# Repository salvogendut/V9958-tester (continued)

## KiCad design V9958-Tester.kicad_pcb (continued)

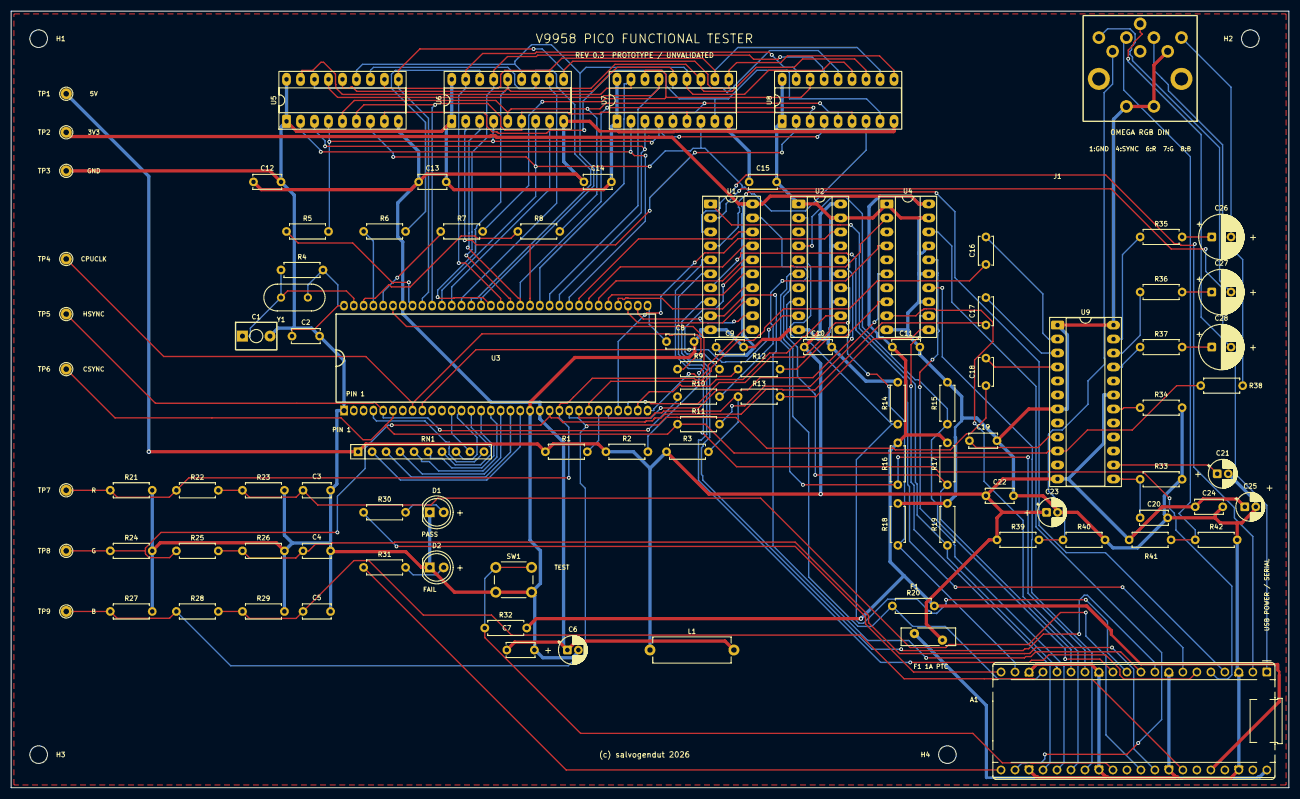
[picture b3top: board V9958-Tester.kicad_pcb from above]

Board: 2 copper layers, 232.0 x 141.0 mm, 101 parts (0 on the bottom side), 116 nets.

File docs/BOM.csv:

Quantity,References,Value / part,KiCad footprint,Notes
1,A1,Raspberry Pi Pico,Module:RaspberryPi_Pico_Common_THT,Original RP2040 Pico module; fit using two 1x20 THT socket strips
1,C1,30pF trimmer,V9958-Tester:C_Trim_P5.00mm,"2-pin ceramic trimmer, 5.0 mm pitch"
1,C2,22pF,Capacitor_THT:C_Disc_D5.0mm_W2.5mm_P5.00mm,
3,C3 C4 C5,10n,Capacitor_THT:C_Disc_D5.0mm_W2.5mm_P5.00mm,
1,C6,100uF,Capacitor_THT:CP_Radial_D5.0mm_P2.00mm,
13,C7 C9 C10 C11 C12 C13 C14 C15 C16 C17 C18 C19 C20,100n,Capacitor_THT:C_Disc_D5.0mm_W2.5mm_P5.00mm,
1,C8,100n VBB,Capacitor_THT:C_Disc_D5.0mm_W2.5mm_P5.00mm,
1,C21,10uF,Capacitor_THT:CP_Radial_D5.0mm_P2.00mm,
1,C22,100n VCC1,Capacitor_THT:C_Disc_D5.0mm_W2.5mm_P5.00mm,
1,C23,47uF VCC1,Capacitor_THT:CP_Radial_D5.0mm_P2.00mm,
1,C24,100n VCC2,Capacitor_THT:C_Disc_D5.0mm_W2.5mm_P5.00mm,
1,C25,47uF VCC2,Capacitor_THT:CP_Radial_D5.0mm_P2.00mm,
3,C26 C27 C28,220uF,Capacitor_THT:CP_Radial_D8.0mm_P3.50mm,
1,D1,GREEN PASS,LED_THT:LED_D5.0mm,
1,D2,RED FAIL,LED_THT:LED_D5.0mm,
1,F1,Bourns MF-RHT100 PTC 1.0A,Fuse:Fuse_Bourns_MF-RHT100,1.0 A hold / 1.8 A trip resettable fuse
4,H1 H2 H3 H4,M3,MountingHole:MountingHole_3.2mm_M3,
1,J1,OMEGA RGB DIN-8,V9958-Tester:DIN8_Omega_THT,Omega-compatible THT DIN-8 socket; verify the chosen part against the supplied footprint
1,L1,5.6uH,Inductor_THT:L_Axial_L14.0mm_D4.5mm_P15.24mm_Horizontal_Fastron_LACC,
12,R1 R2 R3 R14 R15 R16 R17 R18 R19 R20 R32 R40,10k,Resistor_THT:R_Axial_DIN0207_L6.3mm_D2.5mm_P7.62mm_Horizontal,
1,R4,470k,Resistor_THT:R_Axial_DIN0207_L6.3mm_D2.5mm_P7.62mm_Horizontal,
4,R5 R6 R7 R8,100,Resistor_THT:R_Axial_DIN0207_L6.3mm_D2.5mm_P7.62mm_Horizontal,
8,R9 R10 R11 R12 R13 R30 R31 R39,1k,Resistor_THT:R_Axial_DIN0207_L6.3mm_D2.5mm_P7.62mm_Horizontal,
3,R21 R24 R27,470,Resistor_THT:R_Axial_DIN0207_L6.3mm_D2.5mm_P7.62mm_Horizontal,
6,R22 R23 R25 R26 R28 R29,22k,Resistor_THT:R_Axial_DIN0207_L6.3mm_D2.5mm_P7.62mm_Horizontal,
1,R33,47k,Resistor_THT:R_Axial_DIN0207_L6.3mm_D2.5mm_P7.62mm_Horizontal,
1,R34,16k 1% PAL,Resistor_THT:R_Axial_DIN0207_L6.3mm_D2.5mm_P7.62mm_Horizontal,1% metal-film resistor for CXA1645 PAL filter reference
3,R35 R36 R37,75,Resistor_THT:R_Axial_DIN0207_L6.3mm_D2.5mm_P7.62mm_Horizontal,
1,R38,1k sync/75R load,Resistor_THT:R_Axial_DIN0207_L6.3mm_D2.5mm_P7.62mm_Horizontal,Forms approximately 0.35 V CSYNC when terminated by 75 ohms at the display
1,R41,120,Resistor_THT:R_Axial_DIN0207_L6.3mm_D2.5mm_P7.62mm_Horizontal,
1,R42,180,Resistor_THT:R_Axial_DIN0207_L6.3mm_D2.5mm_P7.62mm_Horizontal,
1,RN1,10k bussed,Resistor_THT:R_Array_SIP10,10-pin bussed/common SIP network; common pin is pin 1
1,SW1,TEST,Button_Switch_THT:SW_PUSH_6mm_H7.3mm,
1,TP1,5V,TestPoint:TestPoint_THTPad_D2.0mm_Drill1.0mm,
1,TP2,3V3,TestPoint:TestPoint_THTPad_D2.0mm_Drill1.0mm,
1,TP3,GND,TestPoint:TestPoint_THTPad_D2.0mm_Drill1.0mm,
1,TP4,CPUCLK,TestPoint:TestPoint_THTPad_D2.0mm_Drill1.0mm,
1,TP5,HSYNC,TestPoint:TestPoint_THTPad_D2.0mm_Drill1.0mm,
1,TP6,CSYNC,TestPoint:TestPoint_THTPad_D2.0mm_Drill1.0mm,
1,TP7,RED,TestPoint:TestPoint_THTPad_D2.0mm_Drill1.0mm,
1,TP8,GREEN,TestPoint:TestPoint_THTPad_D2.0mm_Drill1.0mm,
1,TP9,BLUE,TestPoint:TestPoint_THTPad_D2.0mm_Drill1.0mm,
1,U1,SN74LVC245AN,Package_DIP:DIP-20_W7.62mm_Socket_LongPads,"Use LVC, powered at 3.3 V; DIP socket recommended"
1,U2,SN74AHCT244N,Package_DIP:DIP-20_W7.62mm_Socket_LongPads,"Use AHCT, powered at 5 V; DIP socket recommended"
1,U3,V9958 DUT,V9958-Tester:SDIP-64_W19.05mm_P1.778mm_Socket,"DUT; use a quality 64-pin 1.778 mm-pitch, 19.05 mm-row socket/ZIF"
1,U4,SN74LVC244AN,Package_DIP:DIP-20_W7.62mm_Socket_LongPads,"Use LVC, powered at 3.3 V; DIP socket recommended"
1,U5,41464 VRAM L0,Package_DIP:DIP-18_W7.62mm_Socket_LongPads,"64Kx4 DRAM, 120 ns or faster; socket recommended"
1,U6,41464 VRAM H0,Package_DIP:DIP-18_W7.62mm_Socket_LongPads,"64Kx4 DRAM, 120 ns or faster; socket recommended"
1,U7,41464 VRAM L1,Package_DIP:DIP-18_W7.62mm_Socket_LongPads,"64Kx4 DRAM, 120 ns or faster; socket recommended"
1,U8,41464 VRAM H1,Package_DIP:DIP-18_W7.62mm_Socket_LongPads,"64Kx4 DRAM, 120 ns or faster; socket recommended"
1,U9,CXA1645P RGB buffer,Package_DIP:DIP-24_W10.16mm_Socket_LongPads,Sony CXA1645P DIP-24; socket recommended; used for buffered DIN RGB only
1,Y1,21.477270MHz,Crystal:Crystal_HC49-U_Vertical,"Parallel-resonant fundamental crystal, HC49/U THT"

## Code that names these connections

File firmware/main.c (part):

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    PIN_MODE1 = 9,
    PIN_CSW_N = 10,
    PIN_CSR_N = 11,
    PIN_BUS_DIR = 12,
    PIN_BUS_OE_N = 13,
    PIN_VDP_RESET_N = 14,
    PIN_LED_GREEN = 15,
    PIN_LED_RED = 16,
    PIN_CPUCLK = 17,
    PIN_WAIT_N = 18,
    PIN_HSYNC_N = 19,
    PIN_INT_N = 20,
    PIN_CSYNC_N = 21,
    PIN_TEST_N = 22,
    PIN_ADC_R = 26,
    PIN_ADC_G = 27,
    PIN_ADC_B = 28,
};

#define DATA_MASK 0x000000ffu
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static void controls_idle(void) {
    gpio_put(PIN_CSW_N, 1);
    gpio_put(PIN_CSR_N, 1);
    gpio_put(PIN_BUS_OE_N, 1);
    gpio_put(PIN_MODE0, 0);
    gpio_put(PIN_MODE1, 0);
}
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    controls_idle();
    if (!wait_ready_us(100)) return false;
    set_port(port);
    gpio_put(PIN_BUS_DIR, 1);             /* LVC245 A (Pico) -> B (VDP). */
    gpio_set_dir_out_masked(DATA_MASK);
    gpio_put_masked(DATA_MASK, value);
    gpio_put(PIN_BUS_OE_N, 0);
    busy_wait_us_32(1);
    gpio_put(PIN_CSW_N, 0);
    /* 1 us is inside the V9958 186 ns..2 us strobe-width window. */
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    gpio_put(PIN_CSW_N, 1);
    /* 8 us also satisfies the longest documented inter-byte high time. */
    busy_wait_us_32(8);
    gpio_put(PIN_BUS_OE_N, 1);
    gpio_set_dir_in_masked(DATA_MASK);
    return wait_ready_us(100);
}
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    controls_idle();
    if (!wait_ready_us(100)) return false;
    set_port(port);
    gpio_put(PIN_BUS_DIR, 0);             /* LVC245 B (VDP) -> A (Pico). */
    gpio_set_dir_in_masked(DATA_MASK);
    gpio_put(PIN_BUS_OE_N, 0);
    busy_wait_us_32(1);
    gpio_put(PIN_CSR_N, 0);
    busy_wait_us_32(1);
    *value = (uint8_t)(gpio_get_all() & DATA_MASK);
    gpio_put(PIN_CSR_N, 1);
    busy_wait_us_32(8);
    gpio_put(PIN_BUS_OE_N, 1);
    return wait_ready_us(100);
}

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}

static enum test_error run_test(void) {
    gpio_put(PIN_LED_GREEN, 0);
    gpio_put(PIN_LED_RED, 0);
    controls_idle();
    gpio_put(PIN_VDP_RESET_N, 0);
    sleep_ms(20);
    gpio_put(PIN_VDP_RESET_N, 1);
    sleep_ms(50);

    uint16_t cpu, hs, cs;
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static void init_pins(void) {
    for (uint pin = 0; pin <= 22; ++pin) gpio_init(pin);
    gpio_set_dir_in_masked(DATA_MASK);
    for (uint pin = PIN_MODE0; pin <= PIN_LED_RED; ++pin) gpio_set_dir(pin, GPIO_OUT);
    for (uint pin = PIN_CPUCLK; pin <= PIN_TEST_N; ++pin) gpio_set_dir(pin, GPIO_IN);
    gpio_pull_up(PIN_TEST_N);
    controls_idle();
    gpio_put(PIN_BUS_DIR, 0);
    gpio_put(PIN_VDP_RESET_N, 0);
    gpio_put(PIN_LED_GREEN, 0);
    gpio_put(PIN_LED_RED, 0);
    adc_init();
    adc_gpio_init(PIN_ADC_R);
    adc_gpio_init(PIN_ADC_G);
    adc_gpio_init(PIN_ADC_B);
}

int main(void) {
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    enum test_error result = run_test();
    printf("RESULT: %s (code %u)\n", error_name(result), result);
    if (!show_result_screen(result)) puts("DIN RGB result screen could not be displayed");
    gpio_put(PIN_LED_GREEN, result == ERR_NONE);
    gpio_put(PIN_LED_RED, result != ERR_NONE);

    while (true) {
#if V9958_REV_B
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            result = run_test();
            printf("RESULT: %s (code %u)\n", error_name(result), result);
            if (!show_result_screen(result)) puts("RGB result screen could not be displayed");
            gpio_put(PIN_LED_GREEN, result == ERR_NONE);
            gpio_put(PIN_LED_RED, result != ERR_NONE);
        }
#else
        if (!gpio_get(PIN_TEST_N)) {
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                result = run_test();
                printf("RESULT: %s (code %u)\n", error_name(result), result);
                if (!show_result_screen(result)) puts("DIN RGB result screen could not be displayed");
                gpio_put(PIN_LED_GREEN, result == ERR_NONE);
                gpio_put(PIN_LED_RED, result != ERR_NONE);
            }
        }
#endif
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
